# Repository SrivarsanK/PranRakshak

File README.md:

<p align="center">
  
  <br><sub>Concept illustration based on the Stage 2 submission.</sub>
</p>

<p align="center">
  <strong>Worker health, safety, and environmental hazard tracking.</strong><br>
  Vishwakarma Awards 2026–27 · Stage 2 · Team Codemium
</p>

<p align="center">
  <a href="#the-problem">The problem</a> ·
  <a href="#system-architecture">Architecture</a> ·
  <a href="#kicad-schematic">KiCad schematic</a> ·
  <a href="#pcb-layout-draft">PCB layout</a> ·
  <a href="#preliminary-enclosure-fea">FEA study</a> ·
  <a href="#cad-and-design-evidence">CAD gallery</a> ·
  <a href="cad/VKA2026.step">STEP model</a> ·
  <a href="docs/stage-2-submission.pdf">Stage 2 submission</a> ·
  <a href="#roadmap">Roadmap</a>
</p>

## PRAN RAKSHAK

PRAN RAKSHAK is a mine safety project designed to detect underground hazards, warn workers locally, and help rescue teams identify a worker's last-known zone. The proposed system combines helmet-mounted sensing, fixed monitoring nodes, and a Raspberry Pi gateway that can operate without a continuous internet connection.

Its scope covers methane, carbon monoxide, and hydrogen sulfide monitoring, with dust exposure and mine-runoff quality monitoring included in the wider environmental design. A panic button and motion-based man-down detection support worker distress alerts.

> **Current stage:** CAD, schematic, preliminary PCB design, and an assumption-based lid FEA study. Native files, numerical outputs, plots, and check reports are published. The schematic and PCB remain different design variants. Material and loading for the FEA are illustrative; firmware, calibration, and physical field validation remain pending.

## The problem

Underground miners can encounter toxic gases and respirable dust in areas with intermittent communication and limited visibility. Manual checks leave gaps between readings. If a worker becomes unresponsive, a team also needs to know where to search.

The Stage 2 submission identifies three connected monitoring gaps:

- Gas and dust exposure can build up between handheld inspections.
- Separate monitoring and communication systems delay distress alerts and worker location updates.
- Mine runoff may reach surrounding waterways before manual water-quality checks identify contamination.

PRAN RAKSHAK is intended for miners, ventilation officers, environmental monitoring teams, and rescue squads working across tunnels and nearby catchment areas.

## The proposed solution

Helmet-mounted nodes monitor conditions close to each worker. Fixed nodes extend environmental coverage through the mine. Both feed a local gateway for logging and supervision, while node-level threshold checks support alarms during a gateway connection loss.

| Capability | Proposed behavior |
| --- | --- |
| Hazard monitoring | Sample CH4, CO, and H2S; extend sensing to dust and runoff quality as those subsystems are defined. |
| Worker warnings | Trigger local buzzer/vibration alerts and display warnings when configured thresholds are crossed. |
| Emergency signaling | Send a manual panic event or an automatic man-down event after sustained inactivity. |
| Underground localization | Associate workers with nearby node zones on a mapped tunnel layout; retain last-seen information. |
| Offline supervision | Run the MQTT broker, rules, monitoring interface, and logs on an on-site Raspberry Pi. |
| Fault visibility | Flag missing nodes, stale packets, sensor faults, and low-power conditions. |

The submission also proposes airflow-aware leak-source estimation and early anomaly detection. These require ventilation measurements, calibration data, and validation beyond the current CAD model.

## System architecture

The diagram summarizes the proposed data flow in the submission. It does not represent software already included in this repository.

```mermaid
flowchart TD
    subgraph underground[Underground sensing]
        gases["Gas sensors: CH4 / CO / H2S"]
        distress["Motion sensor + panic button"]
        helmet["Helmet node / ESP32-C3<br/>Threshold checks + timestamps"]
        fixed["Fixed environmental nodes<br/>Gas / planned dust and runoff sensing"]
        local["Local worker alert<br/>Buzzer / vibration / display"]
        gases --> helmet
        distress --> helmet
        helmet --> local
    end

    helmet --> network["Local wireless network<br/>Wi-Fi + MQTT / proposed mesh"]
    fixed --> network
    network --> gateway["Raspberry Pi 4<br/>Mosquitto MQTT broker"]
    gateway --> rules["Threshold rules + health checks<br/>Timestamp validation"]
    rules --> logs["Offline telemetry logs"]
    rules --> supervisor["Supervisor interface<br/>OLED / siren / alerts"]
    rules --> zones["Tunnel map + node zones<br/>Worker last-seen status"]
    gateway -->|"Warnings over the local network"| helmet
```

1. A node captures sensor readings and attaches a timestamp and node identity.
2. The controller checks local alarm conditions and sends telemetry over the local network.
3. The gateway validates incoming data, applies rules, and records readings offline.
4. Supervisors receive hazard and node-health information; worker positions are associated with mapped zones.

Wi-Fi/MQTT is the baseline communication design. Multi-hop routing, Kinetic Mesh, and alternative radio fallbacks appear in the submission as proposed extensions; their implementation and underground coverage remain to be demonstrated.

## Hardware and software design

The table describes the four-sheet schematic design. The separate [PCB carrier draft](#pcb-layout-draft) uses a different ADC, GPIO map, and external power arrangement.

| Subsystem | Design or proposal | Status |
| --- | --- | --- |
| Controller | ESP32-C3-WROOM-02-N4 with boot/reset circuit, native USB, and battery-state monitoring. | Schematic complete; firmware and bring-up pending. |
| Gas sensing | MQ-4 (methane) and MQ-7B (CO) with signal conditioning and heater control; conditioned H2S module interface. | Calibration, heater power verification, and final H2S module/AFE selection open. |
| Worker interface | LIS3DH accelerometer, manual panic button, 128 × 64 OLED, and vibration-motor driver. | Man-down algorithm, thresholds, and false-alarm testing pending. |
| Environmental scope | Proposed SPS30 dust interface; temperature/humidity component in CAD; runoff subsystem unspecified. | Sensor suitability and packaging unresolved. |
| Power | Protected pack interface, TP4056 charging, charge/run switch, boost converter, and regulated rails. | Bench verification and runtime measurement pending. |
| Local gateway | Raspberry Pi 4, Mosquitto MQTT, microSD logging, OLED or display, and siren/alert output. | Proposed software architecture and wiring require implementation. |
| Enclosure | STEP assembly with removable lid and mounting standoffs. | Packaging, material choice, sensor access, sealing, and mounting unresolved. |

## KiCad schematic

The [Revision A KiCad package](hardware/README.md) contains a four-sheet, editable ESP32-C3 node design. It includes project-local symbols, a reference-level BOM, the exported netlist, and electrical verification records. Proposed parts and unresolved interfaces are identified in its [design notes](hardware/kicad/Design_Notes.md).

*Main controller sheet. Open the [four-page schematic PDF](hardware/kicad/Schematic_Review.pdf) for readable details and the power, gas-sensor, and user/environment sheets.*

| Sheet | Contents |
| --- | --- |
| [PRAN_RAKSHAK.kicad_sch](hardware/kicad/PRAN_RAKSHAK.kicad_sch) | ESP32-C3 controller, boot/reset, native USB, battery monitoring, and child-sheet hierarchy. |
| [Power.kicad_sch](hardware/kicad/Power.kicad_sch) | Protected pack interface, TP4056 charging, charge/run switch, boost converter, and regulators. |
| [Gas_Sensors.kicad_sch](hardware/kicad/Gas_Sensors.kicad_sch) | MQ-4/MQ-7B signal conditioning, heater selection, and conditioned H2S module interface. |
| [User_And_Environment.kicad_sch](hardware/kicad/User_And_Environment.kicad_sch) | Proposed SPS30 dust interface, LIS3DH accelerometer, OLED, panic input, and vibration-motor driver. |

Download the [complete KiCad ZIP](hardware/PRAN_RAKSHAK_KiCad.zip), or use the cloned repository. In KiCad 10, open [`hardware/kicad/PRAN_RAKSHAK.kicad_pro`](hardware/kicad/PRAN_RAKSHAK.kicad_pro), then open the schematic. Keep all four sheets, `PRAN.kicad_sym`, and `sym-lib-table` together.

| Design evidence | Result or file |
| --- | --- |
| Native KiCad ERC | **0 electrical errors, 68 footprint-review warnings, no exclusions or ignored checks**, reproduced with KiCad 10.0.7 after importing the package into this repository. |
| Remaining schematic warnings | Unassigned footprints; footprint selection is still required for this schematic. Its ERC result does not validate the separate PCB draft. |
| Verification record | [Original ERC JSON](hardware/kicad/ERC_Report.json) and [verification notes](hardware/kicad/Verification.md), which record 125 connection/structure checks. |
| Bill of materials | [Full BOM](hardware/kicad/BOM.csv) and [short BOM with proposed selections](hardware/kicad/Short_BOM.md); prices have not been quoted. |

The four-sheet Revision A design is a bench schematic. Its calculations estimate approximately **2.4–3.1 hours** of runtime under the stated load assumptions, below the eight-hour target. The proposed MQ-7B's **150-second heater cycle** also prevents a guaranteed fresh CO measurement within ten seconds across all phases. The H2S cell/AFE remains an open design item. See the [electrical design notes](hardware/kicad/Design_Notes.md) before building. The separate layout below has not been matched to this schematic.

## PCB layout draft

The [standalone PCB package](hardware/pcb/README.md) contains an editable **52 × 88 mm, two-layer carrier board** with 49 footprint instances and 27 named electrical nets. It places an ESP32-C3 module, ADS1115 external ADC, sensor headers, and alarm-driver circuitry, with preliminary copper routing and antenna keepouts.

<p align="center">
  
  <br><sub>Supplied programmatic placement/copper preview. This is a layout draft, not a DRC screenshot or fabricated board.</sub>
</p>

| PCB deliverable | Link or status |
| --- | --- |
| Editable board | [PRAN_RAKSHAK_RevA.kicad_pcb](hardware/pcb/PRAN_RAKSHAK_RevA.kicad_pcb) — open directly in KiCad PCB Editor. |
| Complete source package | [Download the original PCB ZIP](hardware/PRAN_RAKSHAK_KiCad_RevA_Design_Package.zip). All seven supplied files are preserved. |
| Components and connections | [PCB BOM](hardware/pcb/PRAN_RAKSHAK_RevA_BOM.csv) and [pad-to-net mapping](hardware/pcb/PRAN_RAKSHAK_RevA_Net_Mapping.csv). |
| Original design records | [Supplied README](hardware/pcb/PRAN_RAKSHAK_RevA_README.md), [routing summary](hardware/pcb/PRAN_RAKSHAK_routing_status.txt), and [generator source](hardware/pcb/build_pran_pcb.py). |
| Native KiCad review | [DRC JSON](hardware/pcb/review/DRC_Report.json), [review conditions](hardware/pcb/review/README.md), and [KiCad layer export](hardware/pcb/review/PCB_Layers.svg). |
| DRC result | **61 rule violations: 5 errors and 56 warnings, plus 33 unconnected items.** Checked with KiCad 10.0.7 after filling zones in memory; the supplied board file was not changed. |

This carrier is **not fabrication-ready**. It requires externally regulated 3.3 V and 5 V supplies and includes no battery charger or battery-protection circuit. Its ADS1115 interface, analog dust placeholder, GPIO assignments, and connector map differ from the four-sheet schematic. It has no matching native schematic in the supplied package; schematic/PCB parity has not been checked. Five default DRC checks remain ignored in this standalone-board review.

Complete the routing, resolve DRC findings, verify footprints and power interfaces, and reconcile the board with a matching schematic before fabrication. The original routing summary is an algorithmic source record; the new native KiCad report records the integration review. Neither design is certified for explosive mine environments.

## Engineering targets

These targets come from the project specification on page 7 of the [Stage 2 submission](docs/stage-2-submission.pdf). They have not been verified by measurements in this repository. The KiCad design notes identify current runtime and CO-sensor timing conflicts with these targets.

| Parameter | Design target |
| --- | --- |
| Gas sampling | 1 Hz for CH4, CO, and H2S |
| End-to-end gas alert | Less than 10 seconds between threshold crossing and helmet warning |
| Battery endurance | 8 hours on a 3.7 V, 2500 mAh LiPo |
| Average node power | Approximately 1 W, with sensor-heater duty cycling proposed |
| Wearable pod envelope | Approximately 52 × 88 × 28 mm and 120 g target; STEP inspection gives a 100 × 70 × 25 mm enclosure and 100 × 70 × 3 mm lid, so packaging remains to be reconciled |
| Ingress protection | IP67 target; no ingress-test evidence supplied |
| Offline logging | At least 7 days at the local gateway |
| Missing-node detection | Flag a node within 30 seconds of lost contact |
| Man-down detection | Trigger after 30 seconds without motion |
| Worker localization | Nearest-node zone on a mapped tunnel network |

## CAD and design evidence

The three supplied screenshots retain the CAD application's component browser and workspace. They show the enclosure arrangement and assembly structure at the time of capture.

| Assembly overview | Enclosure and component tree |
| --- | --- |
|  |  |
| Board placement, gas-sensor module, internal wiring, and exploded lid. | Enclosure and mounting components visible alongside the assembly. |

### Download and inspect the model

- [Download VKA2026.step](https://github.com/SrivarsanK/PranRakshak/raw/refs/heads/main/cad/VKA2026.step)
- [Browse the model in this repository](cad/VKA2026.step)
- [Read the CAD component guide and provenance notes](cad/README.md)

Clone the repository to keep the model and its documentation together:

```bash
git clone https://github.com/SrivarsanK/PranRakshak.git
cd PranRakshak
```

Import `cad/VKA2026.step` into a STEP-compatible CAD application such as Fusion, FreeCAD, or SolidWorks. Units are millimetres. With the lid in its exploded position, inspect the enclosure, component placement, standoffs, and wiring.

The supplied file is a STEP assembly exchange model. The originating application's editable sketches and parametric feature history are separate deliverables and are not included here.

## Preliminary enclosure FEA

An [actual numerical lid-pressure study](simulation/lid-pressure/README.md) has been run using the lid extracted from the STEP assembly. Material and service loading are undecided, so the study uses an **assumed isotropic polymer (E=2000 MPa, ν=0.35), a uniform 10 N downward force, and idealized fixed screw-hole walls**. It is a preliminary setup, with no material-strength or safety pass claimed.

| Study output | Published result |
| --- | --- |
| Geometry | Actual lid: 100 × 70 × 3 mm, four 3.5 mm holes. |
| Solves | Four meshes: 2,449, 3,490, 4,822, and 7,411 tetrahedra. Final mesh: 14,188 quadratic displacement nodes and 42,564 DOFs. |
| Conditional centre deflection | 0.06623 mm under the assumed material, supports, and 10 N load. |
| Selected convergence check | Centre deflection and a fixed central stress-probe measure each changed by less than 2% for two successive refinements; final changes were 0.319% and 0.096%. |
| Numerical checks | Analytical uniaxial-tension solver/probe check passed; force balance and free-DOF residual checked for each lid solve. |
| Files | [Visual report](simulation/lid-pressure/Report.html), [detailed study](simulation/lid-pressure/README.md), [mesh statistics CSV](simulation/lid-pressure/results/mesh_statistics.csv), [editable assumptions](simulation/lid-pressure/study.json), and [complete study ZIP](simulation/PranRakshak_Preliminary_Lid_FEA.zip). |

Tagged Gmsh meshes, VTU fields, full solution coefficients, mesher logs, and source code are included. Convergence applies to the two selected measures; it is not an absolute error bound or proof that clamp-region maximum stress has converged. This isolated-lid static study establishes no drop resistance, enclosure sealing, helmet compliance, or intrinsic-safety certification.

## Safety and reliability plan

The submission describes the following protections for implementation and testing:

| Failure condition | Planned response |
| --- | --- |
| Sensor drift, failure, or a stuck reading | Calibration checks, plausibility checks, and an explicit sensor-fault alert. |
| Node loses its gateway connection | Continue local threshold alarms; retry communication and flag the missing node at the gateway. |
| Stale or clock-skewed telemetry | Timestamp packets and reject stale data before localization; the FMEA proposes a 10-second cutoff. |
| Low battery or brownout | Monitor supply state, issue a low-power warning, and test watchdog/reset behavior. |
| Gateway failure | Preserve node-level alarms and identify loss of central monitoring. |
| Ventilation changes or poor node placement | Update the tunnel map and airflow assumptions, then repeat localization tests. |

Intrinsic safety, flame protection, enclosure sealing, and impact resistance require further engineering and test evidence. No mining-equipment certification is claimed by the materials in this repository.

## Roadmap

The schedule below follows the submission's October 2026–January 2027 fabrication plan. Schematic and standalone PCB drafts are now published, along with ERC and DRC evidence. Matching the two designs, completing routing, resolving checks, procurement, and calibration remain open.

| Period | Planned work | Evidence to publish |
| --- | --- | --- |
| October 2026 | Reconcile the schematic and PCB variants, complete routing, resolve footprints and open interfaces, procure components, and bench-calibrate sensors. | Native schematic and PCB drafts, BOMs, ERC, and failing DRC report published; final design, quotes, and calibration records pending. |
| November 2026 | Assemble four sensor nodes and the helmet unit; bring up the Pi gateway, broker, display, and alarms. | Assembly photos, firmware, gateway configuration, and timestamped telemetry. |
| December 2026 | Test connectivity, node loss, man-down detection, watchdogs, brownouts, and corridor localization. | Integration logs and measured alert/localization behavior. |
| January 2027 | Run endurance and drift tests, tune the system, and prepare the Stage 3 demonstration. | Battery measurements, soak-test records, and demonstration evidence. |

## Repository contents

```text
PranRakshak/
├── README.md
├── assets/
│   ├── pran-rakshak-banner.png
│   ├── readme/
│   │   └── (SVG visuals)
│   ├── cad/
│   │   ├── assembly-wiring.jpeg
│   │   ├── assembly-overview.jpeg
│   │   └── enclosure-components.jpeg
│   ├── schematic/
│   │   └── esp32-c3-overview.png
│   └── pcb/
│       └── pcb-overview.png
├── cad/
│   ├── README.md
│   └── VKA2026.step
├── hardware/
│   ├── README.md
│   ├── PRAN_RAKSHAK_KiCad.zip
│   ├── PRAN_RAKSHAK_KiCad_RevA_Design_Package.zip
│   ├── kicad/                    # Four-sheet schematic project and verification records
│   └── pcb/                      # Separate carrier board, source files, and native DRC review
├── simulation/
│   ├── PranRakshak_Preliminary_Lid_FEA.zip
│   └── lid-pressure/             # Assumptions, solver, report, meshes, fields, and convergence plots
└── docs/
    ├── banner-design.md
    ├── design-notes.md
    └── stage-2-submission.pdf
```

For the evidence inventory, source-page mapping, and unresolved specification details, see [design notes](docs/design-notes.md).

## Team and submission

| Field | Details |
| --- | --- |
| Project | PRAN RAKSHAK |
| Team | Codemium |
| Team leader | Kaaviya Varshini V |
| Team ID | VK26-IITH-SM-0275 |
| Event | Vishwakarma Awards 2026–27, Stage 2 |
| Theme | Theme 5: Sustainable Mining — Worker Health, Safety & Environmental Hazard Tracking |

## Sources and acknowledgements

The team's [Stage 2 submission PDF](docs/stage-2-submission.pdf) supplies the project scope and specifications; the CAD screenshots and STEP model document the supplied design. Template examples are excluded as evidence of completed work.

The [Revision A electrical design notes](hardware/kicad/Design_Notes.md) document the KiCad schematic's engineering choices, calculations, and component datasheet references. These proposed choices are distinguished from the submission's requirements.

The separate PCB package was supplied through [Explain KiCad EDA Layout](https://chatgpt.com/share/6ade29ec-7dcc-83ee-a8ff-30b51f544990). Its [source README](hardware/pcb/PRAN_RAKSHAK_RevA_README.md) records the carrier-board assumptions; the [repository review](hardware/pcb/review/README.md) adds the native KiCad DRC result.

The [preliminary FEA report](simulation/lid-pressure/README.md) records the mechanical study assumptions, source-geometry hash, solver versions, numerical checks, and method references.

<p align="center"><sub>Team Codemium · Engineering toward safer underground work.</sub></p>

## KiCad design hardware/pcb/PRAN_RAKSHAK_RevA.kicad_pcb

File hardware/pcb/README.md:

# Standalone PCB carrier draft

[Project README](../../README.md) · [Hardware designs](../README.md) · [Original PCB ZIP](../PRAN_RAKSHAK_KiCad_RevA_Design_Package.zip)

This is the PCB package supplied through [Explain KiCad EDA Layout](https://chatgpt.com/share/6ade29ec-7dcc-83ee-a8ff-30b51f544990). It contains a partially routed, nominal 52 × 88 mm, two-layer carrier board. The seven source files and original ZIP are preserved unchanged; the `review/` folder adds native KiCad integration evidence.

## Open the board

Open [PRAN_RAKSHAK_RevA.kicad_pcb](PRAN_RAKSHAK_RevA.kicad_pcb) directly in KiCad PCB Editor. The package includes no project configuration or matching schematic. KiCad 10.0.7 successfully loaded it for DRC and layer export.

| Supplied file | Purpose |
| --- | --- |
| [PRAN_RAKSHAK_RevA.kicad_pcb](PRAN_RAKSHAK_RevA.kicad_pcb) | Editable board, footprint placement, preliminary copper, zones, and keepouts. |
| [PRAN_RAKSHAK_RevA_preview.png](PRAN_RAKSHAK_RevA_preview.png) | Source-generated placement/copper illustration; not a KiCad DRC screenshot. |
| [PRAN_RAKSHAK_RevA_BOM.csv](PRAN_RAKSHAK_RevA_BOM.csv) | Board-specific component list. |
| [PRAN_RAKSHAK_RevA_Net_Mapping.csv](PRAN_RAKSHAK_RevA_Net_Mapping.csv) | Board-specific pad-to-net assignments. |
| [PRAN_RAKSHAK_RevA_README.md](PRAN_RAKSHAK_RevA_README.md) | Original design rationale, interfaces, and limitations. |
| [PRAN_RAKSHAK_routing_status.txt](PRAN_RAKSHAK_routing_status.txt) | Original algorithmic routing summary. |
| [build_pran_pcb.py](build_pran_pcb.py) | Supplied generator source, retained without execution during repository integration. |

The original README and routing summary describe the source package's checks. The newer [repository review](review/README.md) records native KiCad DRC performed after import.

## Scope and relationship to the schematic

Both this board and the earlier schematic are labeled Revision A by their source chats. Their circuitry differs:

| Area | This PCB carrier | Earlier four-sheet schematic |
| --- | --- | --- |
| Gas conversion | ADS1115 external ADC. | ESP32-C3 ADC paths. |
| Dust sensing | Analog dust-signal placeholder. | Proposed SPS30 UART interface. |
| Motion | External I2C IMU header. | Proposed LIS3DH circuitry. |
| Power | External regulated 3.3 V and 5 V inputs; no charger, regulator, or battery protection. | Battery interface, TP4056 charging, boost converter, regulators, and heater selection. |
| Pin assignments | Board-specific GPIO and connector map. | Different GPIO and connector assignments. |

The board has not been synchronized with the earlier schematic. Verify the source BOM, pad mapping, footprints, and exact external sensor/power modules before creating or reconciling a matching schematic.

## Native review result

[DRC_Report.json](review/DRC_Report.json) records **61 rule violations (5 errors, 56 warnings), plus 33 unconnected items**. Five default checks remain ignored; schematic parity was not tested. The review filled zones in memory and did not save changes to the supplied board. [PCB_Layers.svg](review/PCB_Layers.svg) is a native KiCad layer export of the stored draft.

This board is not fabrication-ready or certified for explosive mine environments. Finish routing, resolve DRC findings, verify the footprint and antenna design, and validate power and sensor interfaces before fabrication.

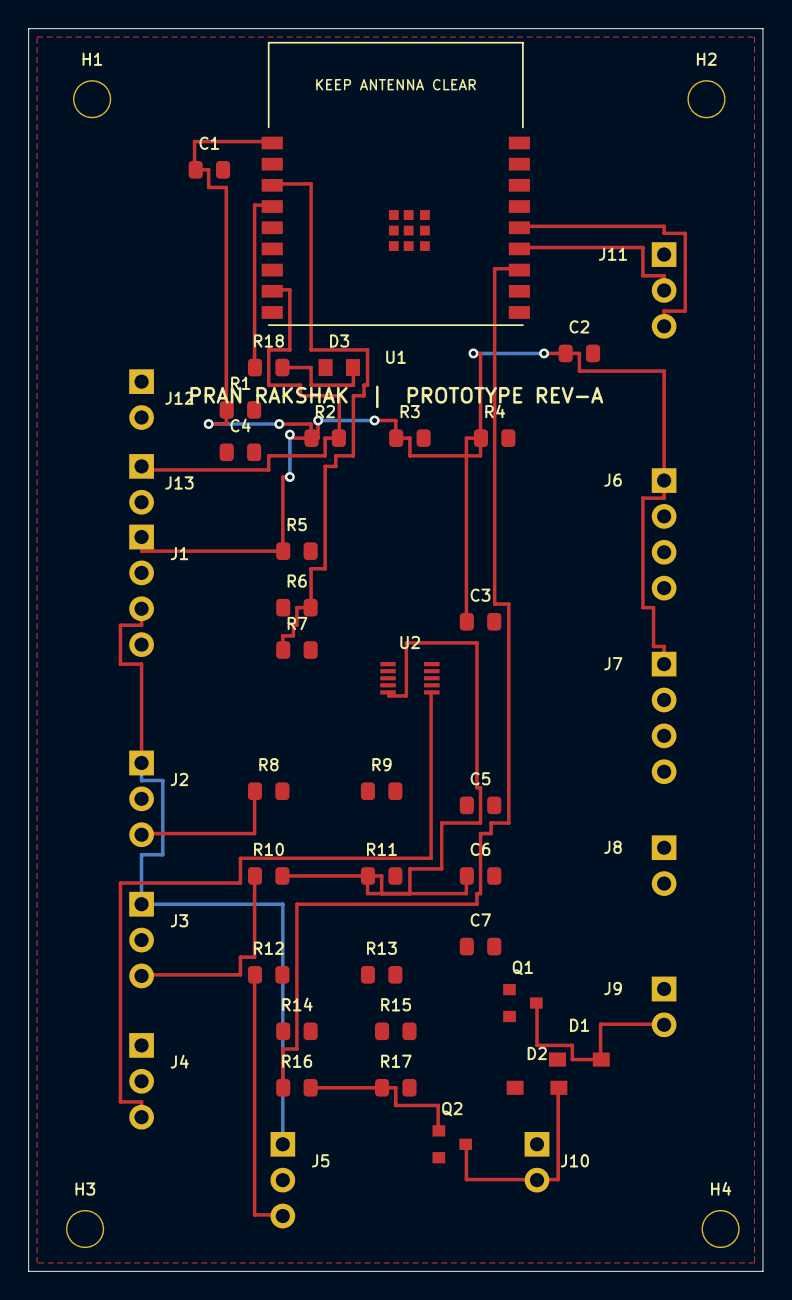
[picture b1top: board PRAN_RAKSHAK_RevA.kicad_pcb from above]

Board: 2 copper layers, 52.0 x 88.0 mm, 49 parts (0 on the bottom side), 27 nets.

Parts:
C1: 10uF; C_0805
C2, C3: 100nF; C_0805
C4: 1uF; C_0805
C5, C6, C7: 10nF; C_0805
D1, D2: SS14; SOD-123
D3: LED_GREEN; LED_0805
H1, H2, H3, H4: MountingHole_2.5mm; MountingHole
J1: Power_In_04; PWR
J2: MQ4_03; MQ4
J3: MQ7_03; MQ7
J4: H2S_AFE_03; H2S
J5: DUST_AFE_03; DUST
J6: I2C_OLED_04; OLED
J7: I2C_IMU_04; IMU
J8: Panic_02; PANIC_SW
J9: Vibration_02; VIB
J10: Buzzer_02; BUZZ
J11: USB_Test_03; USB_TEST
J12: Reset_02; RESET
J13: Boot_02; BOOT
Q1, Q2: AO3400A; SOT-23
R1, R2, R5: 10k; R_0805
R3, R4: 4.7k; R_0805
R6, R7, R15, R17: 100k; R_0805
R8, R10, R12: 12k; R_0805
R9, R11, R13: 20k; R_0805
R14, R16: 100R; R_0805
R18: 1k; R_0805
U1: ESP32-C3-WROOM-02-N4; ESP32-C3-WROOM-02
U2: ADS1115IDGST; VSSOP-10

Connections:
3V3: C1.1, C2.1, C3.1, D1.1, D2.1, J1.1, J4.1, J6.1, J7.1, J9.1, J10.1, R1.1, R2.1, R3.1, R4.1, R5.1, U1.1, U2.8
5V_SENSOR: J1.3, J2.1, J3.1, J5.1
BOOT: J13.1, R2.2, U1.8
BUZZ_GATE: Q2.1, R16.2, R17.1
BUZZ_GATE_SRC: R16.1, U1.12
BUZZ_LOW: D2.2, J10.2, Q2.3
CH4_AIN: C5.1, R8.2, R9.1, U2.4
CH4_RAW: J2.3, R8.1
CO_AIN: C6.1, R10.2, R11.1, U2.5
CO_RAW: J3.3, R10.1
DUST_AIN: C7.1, R12.2, R13.1, U2.7
DUST_RAW: J5.3, R12.1
EN: C4.1, J12.1, R1.2, U1.2
GND: C1.2, C2.2, C3.2, C4.2, C5.2, C6.2, C7.2, D3.1, J1.2, J2.2, J3.2, J4.2, J5.2, J6.2, J7.2, J8.2, J11.1, J12.2, J13.2, Q1.2, Q2.2, R7.2, R9.2, R11.2, R13.2, R15.2, R17.2, U1.9, U1.19, U2.1, U2.3
H2S_AIN: J4.3, U2.6
LED_A: D3.2, R18.2
MOTOR_GATE: Q1.1, R14.2, R15.1
MOTOR_GATE_SRC: R14.1, U1.11
MOTOR_LOW: D1.2, J9.2, Q1.3
PANIC: J8.1, R5.2, U1.10
SCL: J6.4, J7.4, R4.2, U1.6, U2.10
SDA: J6.3, J7.3, R3.2, U1.5, U2.9
STATUS: R18.1, U1.4
USB_DM: J11.2, U1.13
USB_DP: J11.3, U1.14
VBAT_ADC: R6.2, R7.1, U1.3
VBAT_RAW: J1.4, R6.1

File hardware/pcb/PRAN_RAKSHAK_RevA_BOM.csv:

Reference,Value,Footprint/Type,Notes
U1,ESP32-C3-WROOM-02-N4,ESP32-C3-WROOM-02,On-board Wi-Fi antenna - keep metal & copper away
J1,Power_In_04,PWR,Header connector: verify mating pinout
J2,MQ4_03,MQ4,Header connector: verify mating pinout
J3,MQ7_03,MQ7,Header connector: verify mating pinout
J4,H2S_AFE_03,H2S,Header connector: verify mating pinout
J5,DUST_AFE_03,DUST,Header connector: verify mating pinout
J6,I2C_OLED_04,OLED,Header connector: verify mating pinout
J7,I2C_IMU_04,IMU,Header connector: verify mating pinout
J8,Panic_02,PANIC_SW,Header connector: verify mating pinout
J9,Vibration_02,VIB,Header connector: verify mating pinout
J10,Buzzer_02,BUZZ,Header connector: verify mating pinout
J11,USB_Test_03,USB_TEST,Header connector: verify mating pinout
J12,Reset_02,RESET,Header connector: verify mating pinout
J13,Boot_02,BOOT,Header connector: verify mating pinout
U2,ADS1115IDGST,VSSOP-10,16-bit I2C ADC; address tied to GND
C1,10uF,C_0805,
C2,100nF,C_0805,
C3,100nF,C_0805,
R1,10k,R_0805,
C4,1uF,C_0805,
R2,10k,R_0805,
R3,4.7k,R_0805,
R4,4.7k,R_0805,
R5,10k,R_0805,
R6,100k,R_0805,
R7,100k,R_0805,
R8,12k,R_0805,
R9,20k,R_0805,
R10,12k,R_0805,
R11,20k,R_0805,
R12,12k,R_0805,
R13,20k,R_0805,
C5,10nF,C_0805,
C6,10nF,C_0805,
C7,10nF,C_0805,
R14,100R,R_0805,
R15,100k,R_0805,
Q1,AO3400A,SOT-23,
D1,SS14,SOD-123,
R16,100R,R_0805,
R17,100k,R_0805,
Q2,AO3400A,SOT-23,
D2,SS14,SOD-123,
R18,1k,R_0805,
D3,LED_GREEN,LED_0805,
H1,MountingHole_2.5mm,MountingHole,
H2,MountingHole_2.5mm,MountingHole,
H3,MountingHole_2.5mm,MountingHole,
H4,MountingHole_2.5mm,MountingHole,
